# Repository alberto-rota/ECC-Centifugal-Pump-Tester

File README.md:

# ECC Centrifugal pump compliancy tester
An IR-based device for testing the compliance of ECC centrifugal pumps in terms of the hemolitic/thrombogenic effects of the magnetic impeller unstable rotations. 
Employs an LSTM classifier to distinguish proximity signals from compliant and non-compliant pumps.

_This project is in collaboration with Qura s.r.l._

***
* Active Contributors: **Alberto Rota**, Nicolò Pasini, Silvia Bonomi, Gaia Albani, Elisabetta Criseo
***

## Interface Installation
* Windows: *Link not yet Available* 
* Linux: *Link not yet Available*
You should  to have the links)

**NOTE:** The interface embeds the ML kodel for the compliancy classification, hence at the moment it includes the whole TensorFlow framework. The size of the download is close to 1GB, but will be optimized in the future

**Requirements:** No requirement is necessary. The program runs as a standalone application.

After downloading, copy the folder in the directory of your choice. To run the interface excecute the file `qura_pump_tester`, which opens the following window

***
## How to use this Interface
After being plugged in, the device should be detected automatically in the top-right frame, which becomes green and displays the device name, COM-Port and Baudrate. If the Serial Communication is not initialized correctly, the bottom-right gray frame shows `SERIAL COMMUNICATION: INACTIVE`: check that the device name in the `config` file is correct.
With serial communication estabilished, the workflow to be followed is:
* Press the green **START** button to start recording the signals. Ideally, the **START** button should be pressed when the pump is steadily rotating at 500 rpm. The recordings will be displayed in the cart area in real time
* Press the red **STOP** button to stop the recording. Ideally, the **STOP** button should be pressed when the pump is still rotating at 500 rpm and before stopping the driver motion. After this button is pressed, the AI model performs the classification and displays the output in the bottom-left frame
* Press the orange **SAVE** button to save the recording for the last pump tested on a *.csv* file. The file will be saved in the folder specified in the "Save to:" textbox; if any text is specified in the "Append:" textbox, that same text will be appended to the filename. For example, with:
  - *Save to:* C:\Users\qura\tests
  - *Append:* appended

The file will be saved as:
`C:\Users\qura\tests\DDMMYY_HHMMSS_appended.csv` [DayMonthYear_HourMinutesSeconds]

***

## Project Overview
The device is placed on top of the pump while it is mounted and rotating on the driver. The entity of the fluttering is measured as the distance from the 6 IR phototransistors (OPB730F) placed on the pump roof facing downward. The bell-shaped sensitivity curve of the OPB730F ([see datasheet](https://github.com/alberto-rota/Qura-ECC-Centifugal-Pump-Tester/tree/main/media/OPB730F%20Datasheet.pdf)) suggest an inverse relationship between distance and output voltage. The signals are then aquired by an ESP32 and sent to a computer in serial communication

The acquisition circuit is reported below:

and it has been embedded in a custom-made PCB, which connects to the ESP32 via JST connectors.

## Compliancy assessment
Since no evitent distinction critheria emerge from the acquired signals, an AI-based classifier has been trained by recording the signals from 51 pumps at low (100 rpm) and high (500 rpm) speed.
The model is based on a LSTM architecture. The signal is divided in 75-samples-long windows, sliced from the signals (which may have different length) with a padding of 25. No data-augmentation is performed. After an 8-fold cross validation, the model from the best fold classified a test set with an **accuracy of 88%**. 

*The LSTM model is being developed further, no additonal details on the results are therefore provided*

## Prototype Design

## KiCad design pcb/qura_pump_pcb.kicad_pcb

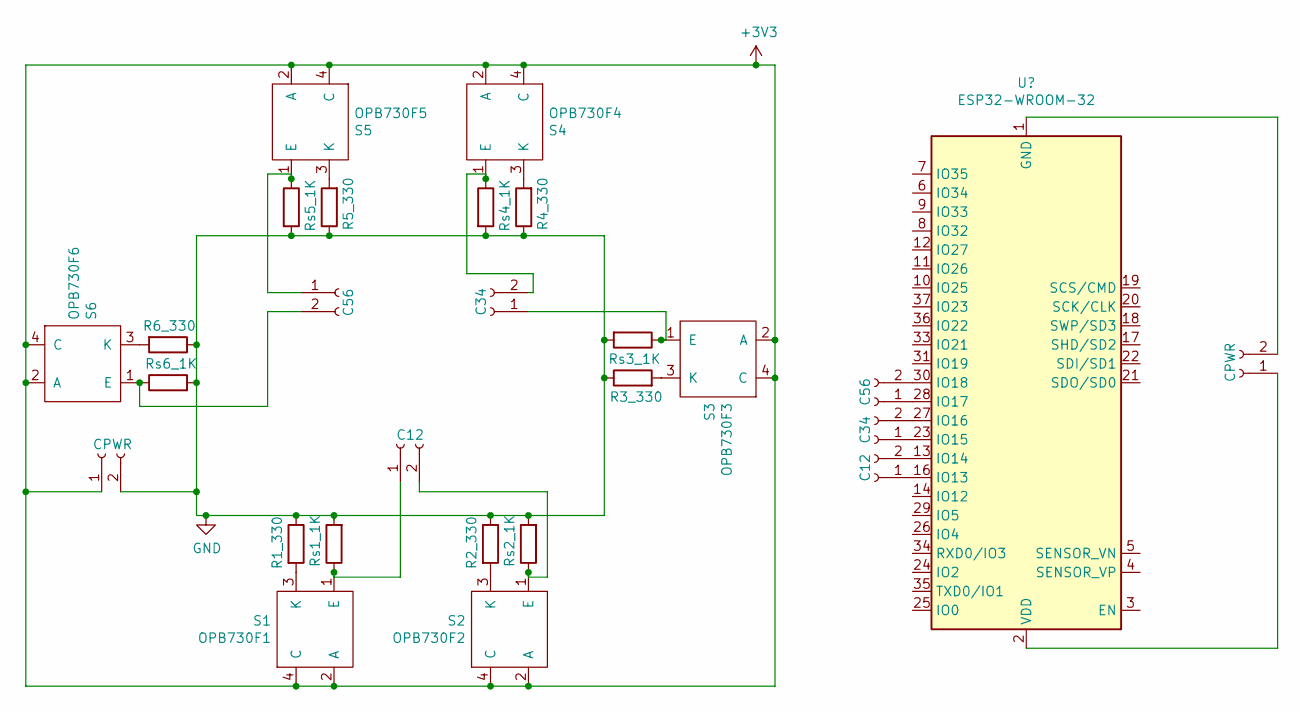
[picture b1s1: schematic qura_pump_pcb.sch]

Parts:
C12: C12; JST_EH_B2B-EH-A_1x02_P2.50mm_Vertical
C34: C34; JST_EH_B2B-EH-A_1x02_P2.50mm_Vertical
C56: C56; JST_EH_B2B-EH-A_1x02_P2.50mm_Vertical
CPWR1: CPWR; JST_EH_B2B-EH-A_1x02_P2.50mm_Vertical
OPB730F1: S1; OPB730F
OPB730F2: S2; OPB730F
OPB730F3: S3; OPB730F
OPB730F4: S4; OPB730F
OPB730F5: S5; OPB730F
OPB730F6: S6; OPB730F
R1: R1_330; R_Axial_DIN0204_L3.6mm_D1.6mm_P7.62mm_Horizontal
R2: R2_330; R_Axial_DIN0204_L3.6mm_D1.6mm_P7.62mm_Horizontal
R3: R3_330; R_Axial_DIN0204_L3.6mm_D1.6mm_P7.62mm_Horizontal
R4: R4_330; R_Axial_DIN0204_L3.6mm_D1.6mm_P7.62mm_Horizontal
R5: R5_330; R_Axial_DIN0204_L3.6mm_D1.6mm_P7.62mm_Horizontal
R6: R6_330; R_Axial_DIN0204_L3.6mm_D1.6mm_P7.62mm_Horizontal
Rs1: Rs1_1K; R_Axial_DIN0204_L3.6mm_D1.6mm_P7.62mm_Horizontal
Rs2: Rs2_1K; R_Axial_DIN0204_L3.6mm_D1.6mm_P7.62mm_Horizontal
Rs3: Rs3_1K; R_Axial_DIN0204_L3.6mm_D1.6mm_P7.62mm_Horizontal
Rs4: Rs4_1K; R_Axial_DIN0204_L3.6mm_D1.6mm_P7.62mm_Horizontal
Rs5: Rs5_1K; R_Axial_DIN0204_L3.6mm_D1.6mm_P7.62mm_Horizontal
Rs6: Rs6_1K; R_Axial_DIN0204_L3.6mm_D1.6mm_P7.62mm_Horizontal

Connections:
+3V3: CPWR1.1, OPB730F1.2 (A), OPB730F1.4 (C), OPB730F2.2 (A), OPB730F2.4 (C), OPB730F3.2 (A), OPB730F3.4 (C), OPB730F4.2 (A), OPB730F4.4 (C), OPB730F5.2 (A), OPB730F5.4 (C), OPB730F6.2 (A), OPB730F6.4 (C); also elsewhere on the board
GND: CPWR1.2, R1.1, R2.1, R3.1, R4.1, R5.1, R6.1, Rs1.2, Rs2.2, Rs3.2, Rs4.2, Rs5.2, Rs6.2; also elsewhere on the board
unnamed: C12.1, OPB730F1.1 (E), Rs1.1
unnamed: C12.2, OPB730F2.1 (E), Rs2.1
unnamed: C34.1, OPB730F3.1 (E), Rs3.1
unnamed: C34.2, OPB730F4.1 (E), Rs4.1
unnamed: C56.1, OPB730F5.1 (E), Rs5.1
unnamed: C56.2, OPB730F6.1 (E), Rs6.1
unnamed: OPB730F1.3 (K), R1.2
unnamed: OPB730F2.3 (K), R2.2
unnamed: OPB730F3.3 (K), R3.2
unnamed: OPB730F4.3 (K), R4.2
unnamed: OPB730F5.3 (K), R5.2
unnamed: OPB730F6.3 (K), R6.2

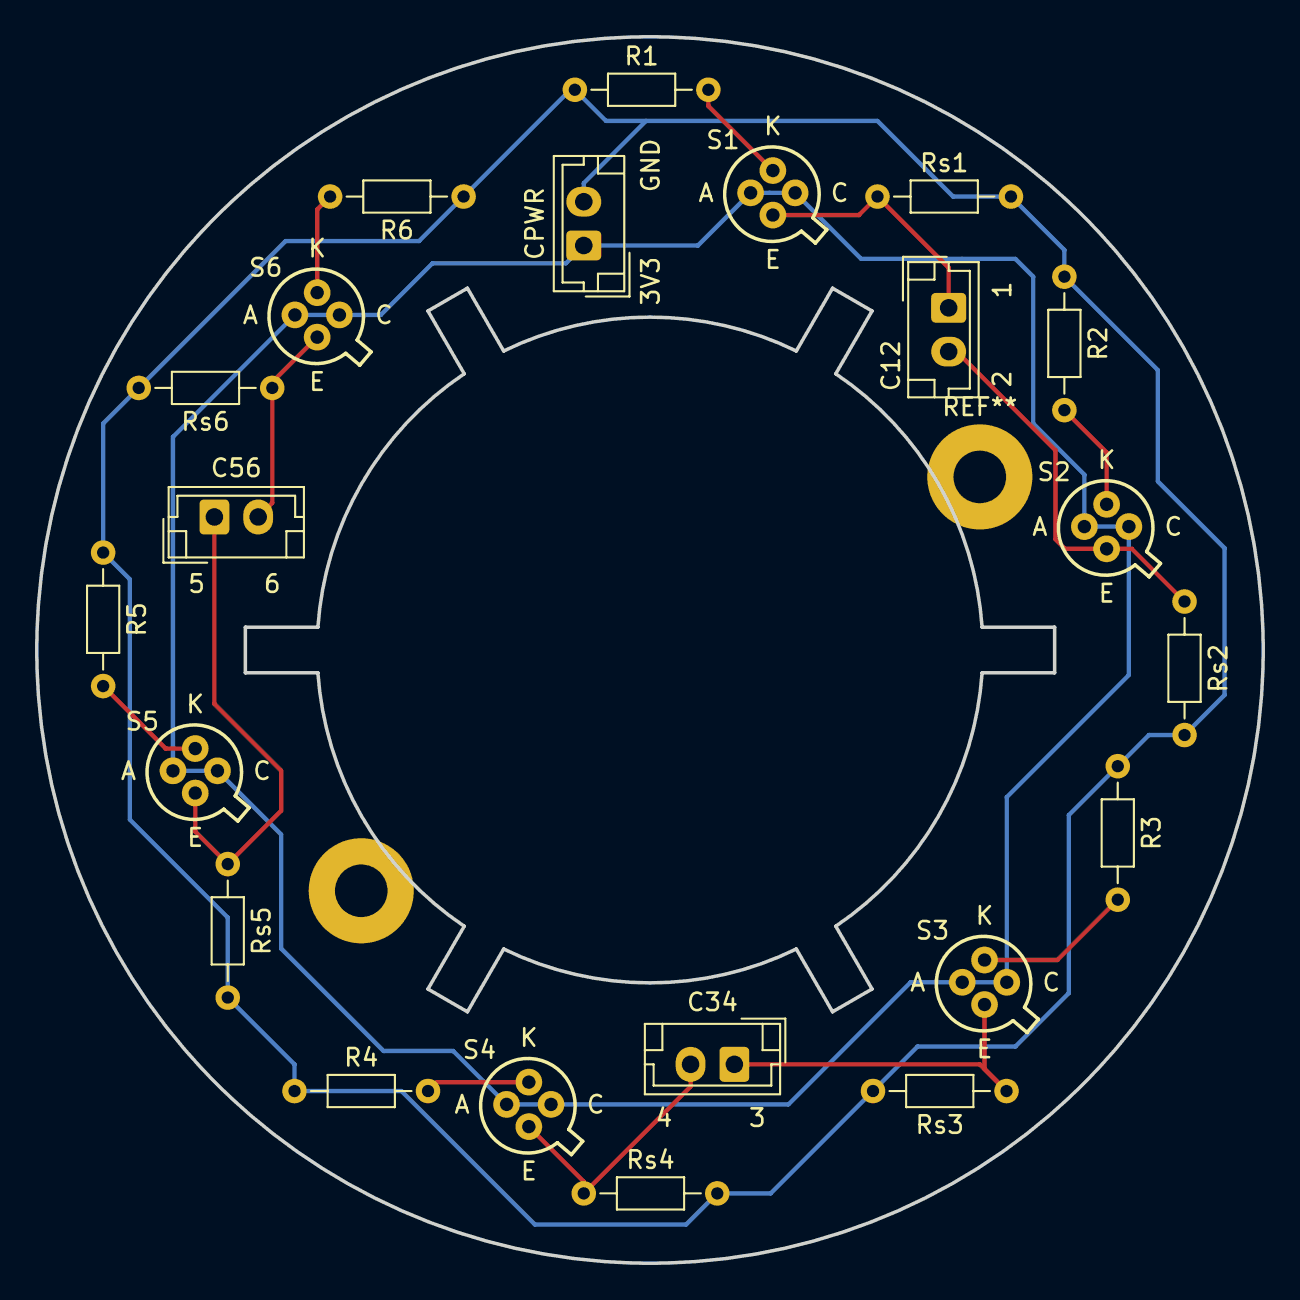
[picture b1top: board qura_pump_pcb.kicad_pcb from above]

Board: 2 copper layers, 70.0 x 70.0 mm, 22 parts (0 on the bottom side), 14 nets.

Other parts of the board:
CPWR: CPWR; JST_EH_B2B-EH-A_1x02_P2.50mm_Vertical

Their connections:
+3V3: CPWR.1; also elsewhere on the board
GND: CPWR.2; also elsewhere on the board

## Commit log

2022-05-13 Merging
